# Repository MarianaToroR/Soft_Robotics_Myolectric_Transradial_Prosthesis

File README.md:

# Soft Robotics Myoelectric Transradial Prosthesis

Open-source repository for the undergraduate thesis **“Soft Robotics Prototype of a Transradial Myoelectric Prosthesis”**, developed by **Mariana Toro Ramírez** and **María Alejandra Mejía Ramírez** as part of the B.Sc. in Mechatronics Engineering at Universidad EIA, under the supervision of Prof. David Rozo Osorio.

## About the Project

This project focused on the design, development, and evaluation of a functional prototype of a transradial myoelectric prosthesis using soft-robotics principles.

The prosthesis integrates mechanical, electronic, signal-processing, and control systems into a single prototype. Its mechanical design uses cable-driven, underactuated mechanisms and flexible structures to reproduce selected movements of the human hand while reducing mechanical and control complexity. The system captures electromyographic (EMG) signals from the user, conditions and digitizes these signals, and processes them through an embedded control system to identify the user's intended action and actuate the prosthetic hand accordingly.

The prototype was designed to perform four common grasp types while incorporating considerations of functionality, ergonomics, robustness, manufacturability, and accessibility. Particular attention was given to the Colombian context and to the potential of rapid-manufacturing and open-source approaches to contribute to the development of more accessible upper-limb prosthetic technologies.

## Repository Contents

This repository contains the files generated throughout the design and development of the prosthesis, including:

- **Mechanical design:** CAD models and files for the socket, palm, fingers, thumb mechanism, and prosthesis assembly.
- **Electronic design:** schematics and PCB design files for the two-channel EMG acquisition and conditioning system, including integration of the MCP3561 analog-to-digital converter and ESP32 microcontroller.
- **PCB manufacturing:** files required for fabrication and assembly of the electronic board, including manufacturing-related documentation.
- **Signal processing and embedded control:** source code for EMG signal acquisition and processing, ADC configuration, grasp classification, and motor control.
- **Simulation files:** electronic simulations used during the design and validation of the EMG signal-conditioning circuitry.

The repository was created as an open-source resource to facilitate the continuation, reproduction, and further development of the project.

## Abstract

This research focuses on the development of a prototype of a transradial myoelectric prosthesis using soft robotics technology for amputated limbs. The relevance of the development focuses on the need to improve the quality of life of the amputated people, highlighting the importance of generating a functional and ergonomic product, mainly framed in the Colombian society and context. The analysis of the current state of the art precedes a detailed description of the adopted methodology. Preliminary research focuses on key aspects such as hand biomechanics and a review of the most recent advances in the field of prosthetics, with emphasis on the use of underactuated transmission and coupled motion architectures. An EMG circuit capable of capturing myoelectric signals, allowing for adaptability to different users and muscles is designed; also, a mechanical design is developed that includes the construction of a socket, palm, and fingers, following the anthropometric characteristics of a mature female user, actuated by cables, which allows performing the movements of abduction and adduction of the thumb, and exion and extension of all fingers, allowing to execute four types of grasps that statistically an average user executes most frequently in their daily activities. A myoelectric control algorithm is developed, which identifies, classifies, and executes the grasps on the user’s demand. Optimization of
the control code and improvements in the mechanical system are suggested for future research. Finally, it is concluded that the project has achieved its objectives in terms of functionality and performance.

**Keywords:** Soft Robotics, Transradial Prosthesis, Myoelectric Signal, EMG.

## Thesis

The complete thesis is available through the Universidad EIA institutional repository:

**Toro Ramírez, M., & Mejía Ramírez, M. A. (2023). _Prototipo en robótica suave de prótesis mioeléctrica transradial_. Universidad EIA.**

https://repository.eia.edu.co/handle/11190/6398

## Authors

**Mariana Toro Ramírez**  
B.Sc. Mechatronics Engineering, Universidad EIA

**María Alejandra Mejía Ramírez**  
B.Sc. Mechatronics Engineering, Universidad EIA

### Thesis Supervisor

**Prof. David Rozo Osorio**  
MEng. Mechatronics, Robotics and Automation Engineering, Universidad Pontificia Bolivariana

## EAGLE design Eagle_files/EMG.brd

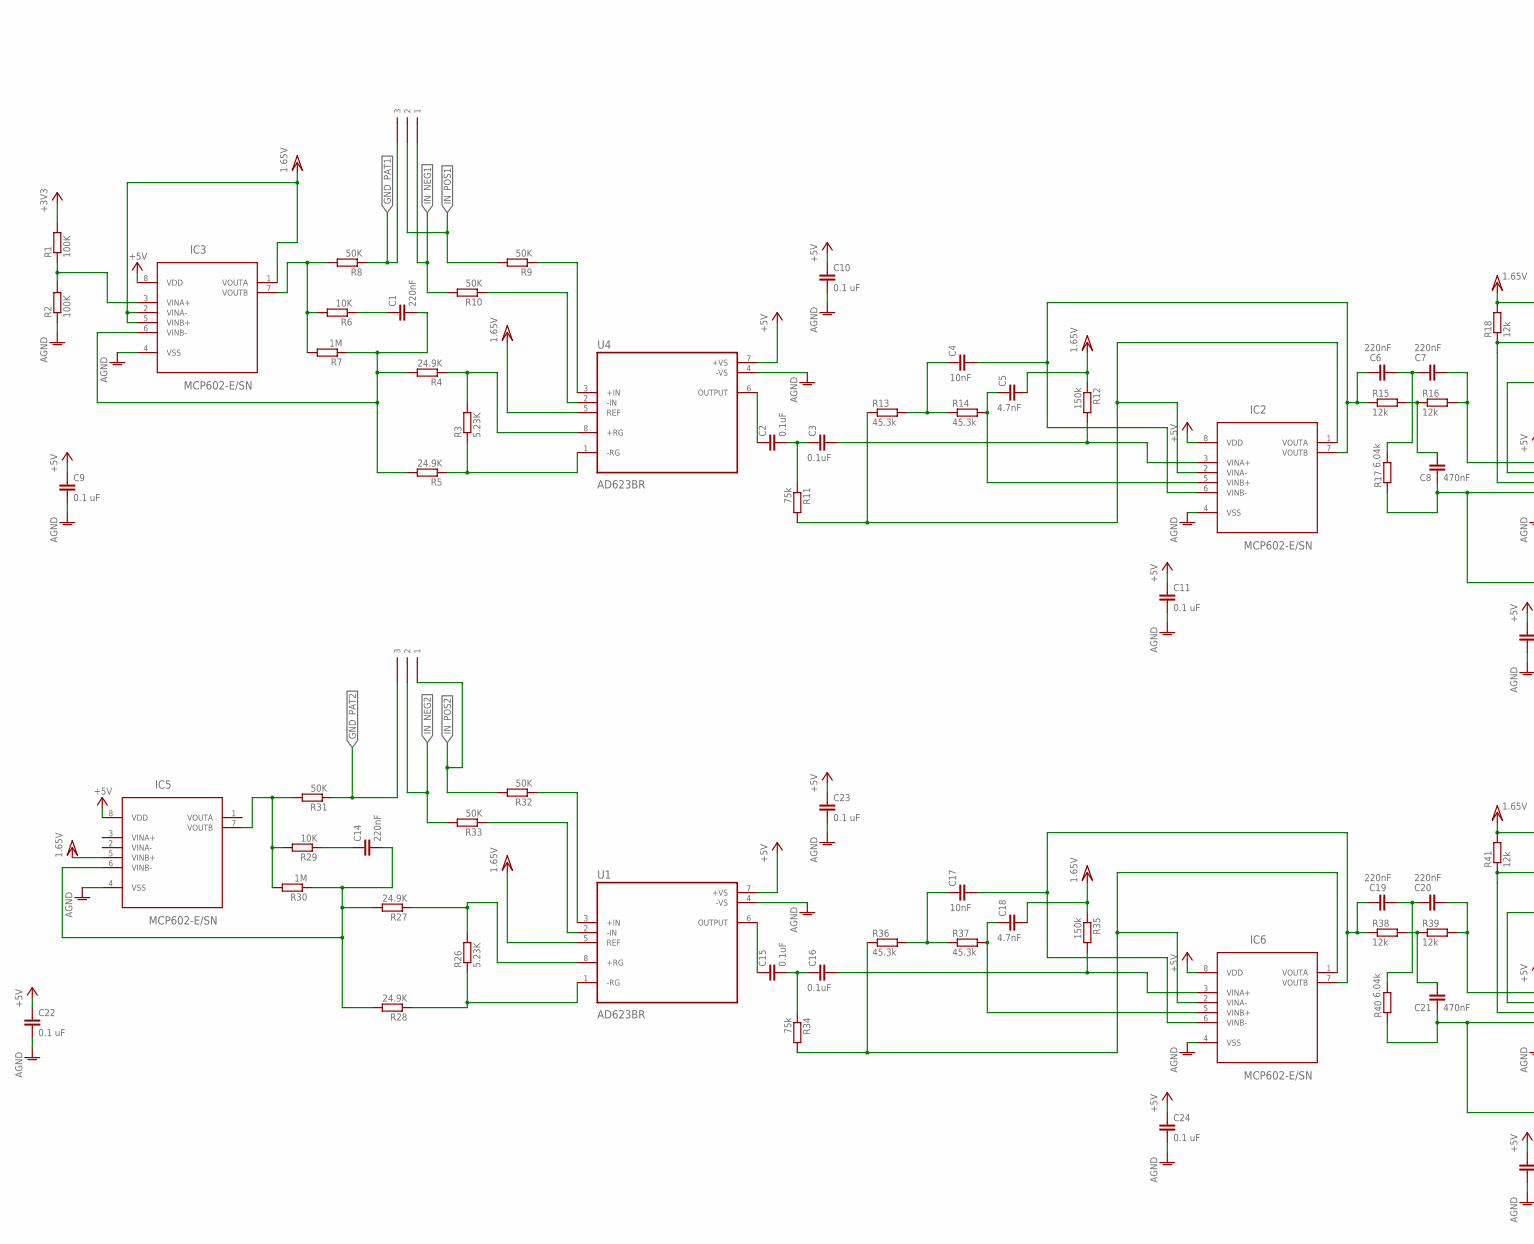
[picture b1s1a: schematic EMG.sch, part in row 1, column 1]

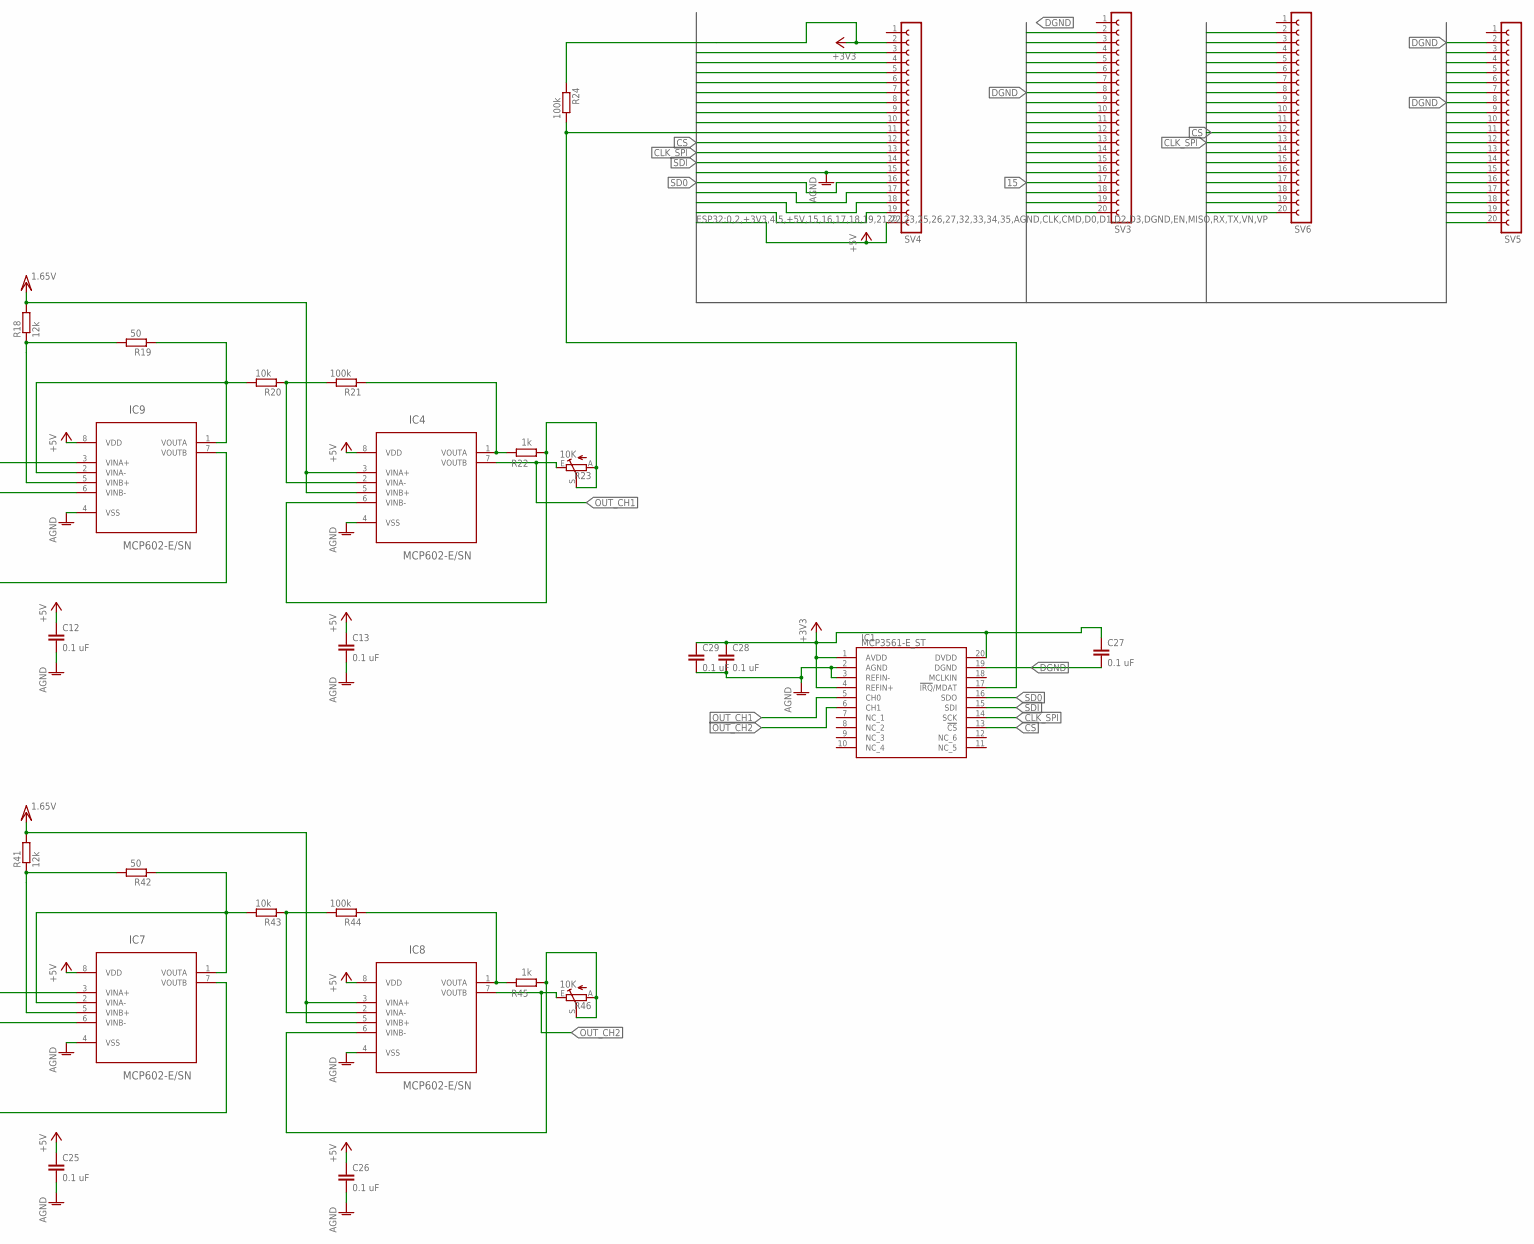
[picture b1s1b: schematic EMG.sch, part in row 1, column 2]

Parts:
C1, C6, C7, C14, C19, C20: 220nF; C0402
C2, C3, C15, C16: 0.1uF; C0402
C4, C17: 10nF; C0402
C5, C18: 4.7nF; C0402
C8, C21: 470nF; C0402
C9, C10, C11, C12, C13, C22, C23, C24, C25, C26, C27, C28, C29: 0.1 uF; C0402
CON1, CON2: PW3; PWR3
IC1: MCP3561-E_ST; SOP65P640X120-20N
IC2, IC3, IC4, IC5, IC6, IC7, IC8, IC9: MCP602-E/SN; SOIC127P600X175-8N
R1, R2: 100K; R0402
R3, R26: 5.23K; R0402
R4, R5, R27, R28: 24.9K; R0402
R6, R29: 10K; R0402
R7, R30: 1M; R0402
R8, R9, R10, R31, R32, R33: 50K; R0402
R11, R34: 75k; R0402
R12, R35: 150k; R0402
R13, R14, R36, R37: 45.3k; R0402
R15, R16, R18, R38, R39, R41: 12k; R0402
R17, R40: 6.04k; R0402
R19, R42: 50; R0402
R20, R43: 10k; R0402
R21, R24, R44: 100k; R0402
R22, R45: 1k; R0402
R23, R46: 10K; CA6V
SV3, SV4, SV5, SV6: FE20-1; FE20
U1, U4: AD623BR; SOIC127P600X175-8N

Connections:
0: SV3.15, SV5.15
2: SV3.16, SV5.16
4: SV3.14, SV5.14
5: SV3.11, SV5.11
15: SV3.17, SV5.17
16: SV3.13, SV5.13
17: SV3.12, SV5.12
18: SV3.10, SV5.10
19: SV3.9, SV5.9
21: SV3.7, SV5.7
22: SV3.4, SV5.4
23: SV3.3, SV5.3
25: SV4.10, SV6.10
26: IC1.17 (!IRQ!/MDAT), R24.2, SV4.11, SV6.11
32: SV4.8, SV6.8
33: SV4.9, SV6.9
34: SV4.6, SV6.6
35: SV4.7, SV6.7
+3V3: C27.1, C28.1, C29.1, IC1.1 (AVDD), IC1.4 (REFIN+), IC1.20 (DVDD), R1.2, R24.1, SV4.2, SV6.2
+5V: C9.1, C10.1, C11.1, C12.1, C13.1, C22.1, C23.1, C24.1, C25.1, C26.1, IC2.8 (VDD), IC3.8 (VDD), IC4.8 (VDD), IC5.8 (VDD), IC6.8 (VDD), IC7.8 (VDD), IC8.8 (VDD), IC9.8 (VDD), SV4.20, SV6.20, U1.7 (+VS), U4.7 (+VS)
AGND: C9.2, C10.2, C11.2, C12.2, C13.2, C22.2, C23.2, C24.2, C25.2, C26.2, C28.2, C29.2, IC1.2 (AGND), IC1.3 (REFIN-), IC2.4 (VSS), IC3.4 (VSS), IC4.4 (VSS), IC5.4 (VSS), IC6.4 (VSS), IC7.4 (VSS), IC8.4 (VSS), IC9.4 (VSS), R2.1, SV4.15, SV6.15, U1.4 (-VS), U4.4 (-VS)
CLK: SV3.20, SV5.20
CLK_SPI: IC1.14 (SCK), SV4.13, SV6.13
CMD: SV4.19, SV6.19
CS: IC1.13 (!CS), SV4.12, SV6.12
D0: SV3.19, SV5.19
D1: SV3.18, SV5.18
D2: SV4.17, SV6.17
D3: SV4.18, SV6.18
DGND: C27.2, IC1.19 (DGND), SV3.2, SV3.8, SV5.2, SV5.8
EN: SV4.3, SV6.3
GND_PAT1: CON2.P$3 (3), R8.1
GND_PAT2: CON1.P$3 (3), R31.1
IN_NEG1: CON2.P$1 (1), R10.2
IN_NEG2: CON1.P$2 (2), R33.2
IN_POS1: CON2.P$2 (2), R9.2
IN_POS2: CON1.P$1 (1), R32.2
unnamed: IC3.3 (VINA+), R1.1, R2.2
unnamed: C1.2, IC3.6 (VINB-), R4.2, R5.2, R7.1
unnamed: R3.1, R5.1, U4.1 (-RG)
unnamed: R3.2, R4.1, U4.8 (+RG)
unnamed: C2.1, U4.6 (OUTPUT)
unnamed: C1.1, R6.1
unnamed: R9.1, U4.3 (+IN)
unnamed: R10.1, U4.2 (-IN)
unnamed: C2.2, C3.1, R11.1
unnamed: IC2.1 (VOUTA), IC2.2 (VINA-), R11.2, R13.1
unnamed: C3.2, IC2.3 (VINA+), R12.2
unnamed: C4.1, R13.2, R14.1
unnamed: IC9.1 (VOUTA), IC9.2 (VINA-), R19.1, R20.2
unnamed: C5.1, IC2.5 (VINB+), R14.2
unnamed: C6.2, C7.1, R17.2
unnamed: C8.2, R15.2, R16.1
unnamed: C4.2, C6.1, IC2.6 (VINB-), IC2.7 (VOUTB), R15.1
unnamed: C7.2, IC9.3 (VINA+), R16.2
unnamed: IC9.5 (VINB+), R18.1, R19.2
unnamed: IC4.2 (VINA-), R20.1, R21.2
unnamed: C8.1, IC9.6 (VINB-), IC9.7 (VOUTB), R17.1
unnamed: IC4.1 (VOUTA), R21.1, R22.1
unnamed: IC4.6 (VINB-), R22.2, R23.A, R23.S
unnamed: C14.2, IC5.6 (VINB-), R27.2, R28.2, R30.1
unnamed: R26.1, R28.1, U1.1 (-RG)
unnamed: R26.2, R27.1, U1.8 (+RG)
unnamed: C14.1, R29.1
unnamed: R32.1, U1.3 (+IN)
unnamed: R33.1, U1.2 (-IN)
unnamed: C15.1, U1.6 (OUTPUT)
unnamed: C15.2, C16.1, R34.1
unnamed: IC6.1 (VOUTA), IC6.2 (VINA-), R34.2, R36.1
unnamed: C16.2, IC6.3 (VINA+), R35.2
unnamed: C17.1, R36.2, R37.1
unnamed: C18.1, IC6.5 (VINB+), R37.2
unnamed: C19.2, C20.1, R40.2
unnamed: C21.2, R38.2, R39.1
unnamed: C17.2, C19.1, IC6.6 (VINB-), IC6.7 (VOUTB), R38.1
unnamed: C20.2, IC7.3 (VINA+), R39.2
unnamed: IC7.1 (VOUTA), IC7.2 (VINA-), R42.1, R43.2
unnamed: C21.1, IC7.6 (VINB-), IC7.7 (VOUTB), R40.1
unnamed: IC7.5 (VINB+), R41.1, R42.2
unnamed: IC8.2 (VINA-), R43.1, R44.2
unnamed: IC8.1 (VOUTA), R44.1, R45.1
unnamed: IC8.6 (VINB-), R45.2, R46.A, R46.S
OUT_CH1: IC1.5 (CH0), IC4.7 (VOUTB), R23.E
OUT_CH2: IC1.6 (CH1), IC8.7 (VOUTB), R46.E
OUT_REF: IC3.7 (VOUTB), R6.2, R7.2, R8.2
OUT_REF1: IC5.7 (VOUTB), R29.2, R30.2, R31.2
RX: SV3.6, SV5.6
SD0: IC1.16 (SDO), SV4.16, SV6.16
SDI: IC1.15 (SDI), SV4.14, SV6.14
TX: SV3.5, SV5.5
VCC/2: C5.2, C18.2, IC3.1 (VOUTA), IC3.2 (VINA-), IC3.5 (VINB+), IC4.3 (VINA+), IC4.5 (VINB+), IC5.5 (VINB+), IC8.3 (VINA+), IC8.5 (VINB+), R12.1, R18.2, R35.1, R41.2, U1.5 (REF), U4.5 (REF)
VN: SV4.5, SV6.5
VP: SV4.4, SV6.4

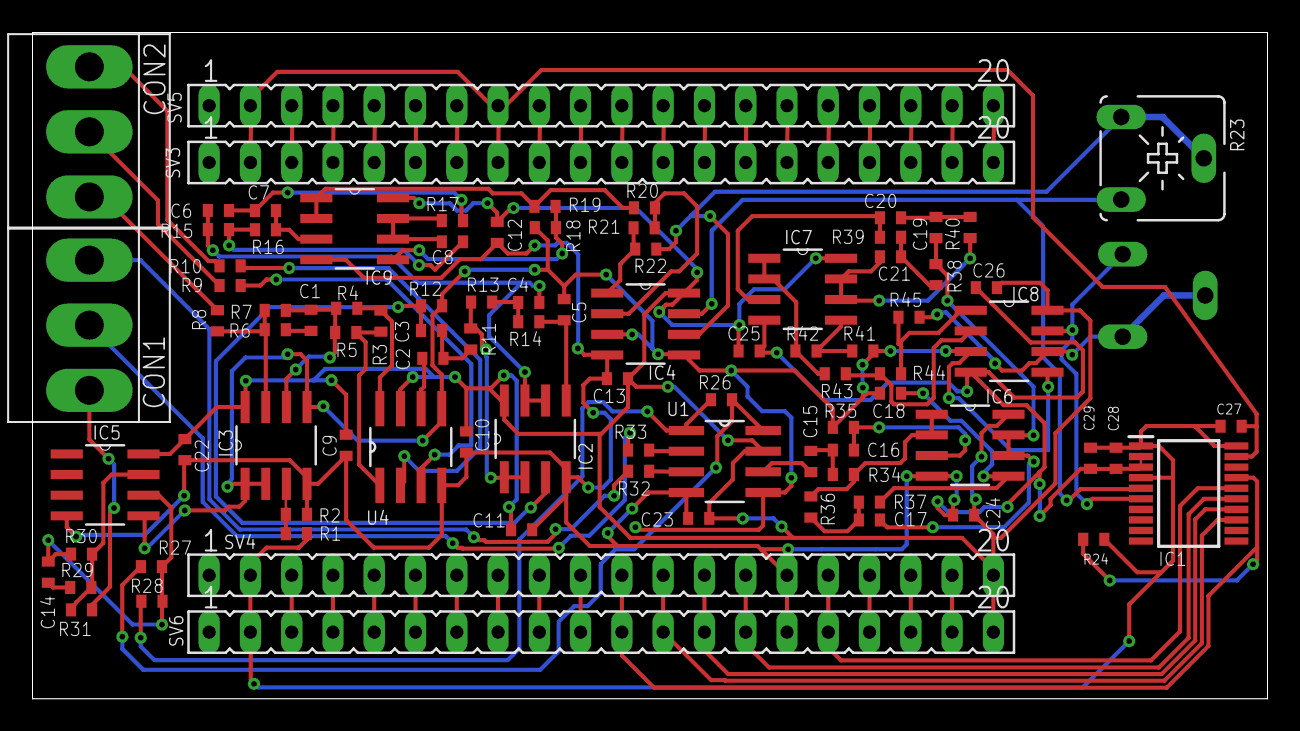
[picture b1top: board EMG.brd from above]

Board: 2 copper layers, 76.0 x 41.0 mm, 91 parts (1 on the bottom side), 93 nets.
